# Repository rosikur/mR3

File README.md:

# mR3

## Before we start

I'm so so incredibly Sorry but the firmware was made by an artifical intelligence. This was the result of pixl.hackclub.com shutting down in which I had to finish my Project as soon as possible

## Introduction

Hey Guys! This is my first Music Player Project. The Goal is to learn how to wire
a DAC(Digital Audio Convertor) without Signal Lose. An Amplifier without Noise.
How to power an Stereo Speaker System. How to cnc machine the chassis and how to
fit everything in a compact chassis with a display.

## Components

# ICs:

- TPA6132ARTE
- PAM8403D
- PCM5120A
- ESP32-S3-WROOM-1
- TPS63802DLAR
- BQ25895RTW
- 2.8" Display(See BOM and PINS MAKE SURE YOU BUY one with the same PIN count)

# Periphals

- 3x THT SW Tactile SPST Angeled
- 6x THT SW Push 6mm H5mm
- 1x USB c 2.o Receptaple
- 1x Audio Jack SwitchTR
- 1x 3.7 V Battary Pack (Must be with BMS)
- SD Card Holder (Wuerth)
- 3w Speakers (2)
- Soldering Iron

## How to build it?

# PCB

Firstly take the gerber.zip and upload them to the PCB manufacturer of your choosing, I prefer JLCPCB as i can use the bom in their daughter company lscs to buy the components.
I really recommend to order a stencil with your order because you'll be miserable soldering IC's

Secondly go to LSCS with the bom file and order everything with their MOQ (Minimum Order Quantity) I really recommend to get extra Components 0805s are really common for lots of Projects, if you follow my projects, you can be sure that we'll be using them.

Thirdly, get some solder paste and a Heatplate if you havn't yet else your closest Hackerspace will have some (Props to the C3PB and CCC)

Fourth, open the PCB on your Laptop and grab tweezers and the pcb
put the stencil on (smh) and spread the paste with an old Credit Card. Make sure to put every componet correctly ESPECIALLY THE BATTERY and the IC's (ESP32 are hella expensive.)

Fifth, select a side which will be easier to solder (the back in our case) add everything and put them on the Heatplate or a reflow oven

Lastly make sure to put the battery in correctly THIS IS VERY IMPORTANT. Add the speakers correctly so they dont play in reverse. that should be about it for the pcb onto the case!

# PCB images

# Case

3d print it CNC it idc, i will be uploading the STL , the 3mf the STEP and the cnc file.
I recommend Prototyping with 3d Print and CNC as a finished Product. I will be Posting both results soon!

The Case is now almost finished, I only need to add the buttons,
Here is how it turned out:

# Firmware

Install esp tool or plattform IO press the boot button and plug it into your Computer if you are using Plattform IO you'll have to compile it first ,for esp tool use the ready .bin files :D once its sent to the ESP its ready to use have fun
(Obviously assemble it first)

# BOM

The complete bill of materials is also available as [`bom.csv`](bom.csv).

| Component              | Designators                                             | Footprint                                                    | Qty. | Supplier                                                                                                                         |
| ---------------------- | ------------------------------------------------------- | ------------------------------------------------------------ | ---: | -------------------------------------------------------------------------------------------------------------------------------- |
| 0.47uF                 | C1, C2                                                  | `C_0805_2012Metric_Pad1.18x1.45mm_HandSolder`                |    2 | [Buy](https://www.tme.eu/de/details/cl21b474kafnnng/kondensatoren-mlcc-smd/samsung/)                                             |
| 2.2uF                  | C3, C4, C8, C9                                          | `C_0805_2012Metric_Pad1.18x1.45mm_HandSolder`                |    4 | [Buy](https://www.tme.eu/de/details/0805b225k160ct/kondensatoren-mlcc-smd/walsin/)                                               |
| 0.1uF                  | C5, C6, C14, C15, C16, C19                              | `C_0805_2012Metric_Pad1.18x1.45mm_HandSolder`                |    6 | [Buy](https://www.tme.eu/de/details/0805b104k500ct/kondensatoren-mlcc-smd/walsin/)                                               |
| 1uF                    | C7, C10, C11, C12, C13, C21, C22, C23, C24, C31         | `C_0805_2012Metric_Pad1.18x1.45mm_HandSolder`                |   10 | [Buy](https://www.tme.eu/de/details/0805b105k250ct/kondensatoren-mlcc-smd/walsin/)                                               |
| 10uF                   | C17, C18, C26                                           | `C_0805_2012Metric_Pad1.18x1.45mm_HandSolder`                |    3 | [Buy](https://www.tme.eu/de/details/c0805c106k9pac/kondensatoren-mlcc-smd/kemet/c0805c106k9pactu/)                               |
| 22uF                   | C20, C28, C29, C32, C33, C34                            | `C_0805_2012Metric_Pad1.18x1.45mm_HandSolder`                |    6 | [Buy](https://www.tme.eu/de/details/jmk212abj226mg-t/kondensatoren-mlcc-smd/taiyo-yuden/)                                        |
| 47nF                   | C27                                                     | `C_0805_2012Metric_Pad1.18x1.45mm_HandSolder`                |    1 | [Buy](https://www.tme.eu/de/details/0805b473k500cg/kondensatoren-mlcc-smd/walsin/)                                               |
| 4.7uF                  | C30                                                     | `C_0805_2012Metric_Pad1.18x1.45mm_HandSolder`                |    1 | [Buy](https://www.tme.eu/de/details/0805x475k6r3ct/kondensatoren-mlcc-smd/walsin/)                                               |
| LED                    | D1                                                      | `LED_0805_2012Metric_Pad1.15x1.40mm_HandSolder`              |    1 | [Buy](https://www.tme.eu/de/details/of-smd2012r/led-dioden-smd-bunt/optoflash/)                                                  |
| Micro SD card          | J1                                                      | `microSD_HC_Wuerth_693072010801`                             |    1 | [Buy](https://www.mouser.de/en/ProductDetail/Wurth-Elektronik/693072010801?qs=7gQLVZk5cPmw4uU1mAcUFg%3D%3D)                      |
| Audio jack             | J2                                                      | `Jack_3.5mm_CUI_SJ1-3515N_Horizontal`                        |    1 | [Buy](https://www.tme.eu/de/details/sj13513/klinken-steckverbinder/same-sky-r/sj1-3513/)                                         |
| 9-pin socket _(DNP)_   | J3                                                      | `PinHeader_1x09_P2.54mm_Vertical`                            |    1 | DNP                                                                                                                              |
| USB-C receptacle       | J4                                                      | `USB_C_Receptacle_Amphenol_12401548E4-2A`                    |    1 | [Buy](https://www.mouser.de/en/ProductDetail/Amphenol-Commercial-Products/12401598E42A?qs=367PjNmvCmllVMBVyIyS3w%3D%3D)          |
| 2-pin connector        | J5                                                      | `JST_PH_S2B-PH-K_1x02_P2.00mm_Horizontal`                    |    1 | [Buy](https://www.tme.eu/de/details/s2b-xh-a-1/signalsteckverbinder-raster-2-50mm/jst/s2b-xh-a-1-lf-sn/)                         |
| 2.2uH inductor         | L1                                                      | `L_2512_6332Metric_Pad1.52x3.35mm_HandSolder`                |    1 | [Buy](https://www.mouser.de/en/ProductDetail/Bourns/SRP2512-2R2M?qs=sGAEpiMZZMukHu%252BjC5l7YdTJBteetShHxC51KzP5FBA%3D)          |
| 0.47uH inductor        | L2                                                      | `L_2512_6332Metric_Pad1.52x3.35mm_HandSolder`                |    1 | [Buy](https://www.mouser.de/en/ProductDetail/652-SRP2512-R47M)                                                                   |
| Speaker                | LS1, LS2                                                | `JST_PH_S2B-PH-K_1x02_P2.00mm_Horizontal`                    |    2 | [Buy](https://a.aliexpress.com/_EJix1bo)                                                                                         |
| 10k resistor           | R1, R2, R4, R5, R6, R7, R9, R10, R13, R14, R16, R22–R33 | `R_0805_2012Metric_Pad1.20x1.40mm_HandSolder`                |   23 | [Buy](https://www.tme.eu/de/details/wr08x1002ftl/smd-widerstaende/walsin/)                                                       |
| 5.1k resistor          | R3, R12                                                 | `R_0805_2012Metric_Pad1.20x1.40mm_HandSolder`                |    2 | [Buy](https://www.tme.eu/de/details/wr08x5101ftl/smd-widerstaende/walsin/)                                                       |
| 1k resistor            | R8, R11                                                 | `R_0805_2012Metric_Pad1.20x1.40mm_HandSolder`                |    2 | [Buy](https://www.tme.eu/de/details/wr08x102jtl/smd-widerstaende/walsin/wr08x102-jtl/)                                           |
| 6.8k resistor          | R15                                                     | `R_0805_2012Metric_Pad1.20x1.40mm_HandSolder`                |    1 | [Buy](https://www.tme.eu/de/details/wr08x6801ftl/smd-widerstaende/walsin/)                                                       |
| 2.2k resistor          | R17                                                     | `R_0805_2012Metric_Pad1.20x1.40mm_HandSolder`                |    1 | [Buy](https://www.tme.eu/de/details/wr08x222jtl/smd-widerstaende/walsin/wr08x222-jtl/)                                           |
| 260 ohm resistor       | R18                                                     | `R_0805_2012Metric_Pad1.20x1.40mm_HandSolder`                |    1 | [Buy](https://www.tme.eu/de/details/rc0805fr-07261rl/smd-widerstaende/yageo/)                                                    |
| 100k resistor          | R19                                                     | `R_0805_2012Metric_Pad1.20x1.40mm_HandSolder`                |    1 | [Buy](https://www.tme.eu/de/details/wr08x1003ftl/smd-widerstaende/walsin/)                                                       |
| 91k resistor           | R20                                                     | `R_0805_2012Metric_Pad1.20x1.40mm_HandSolder`                |    1 | [Buy](https://www.mouser.de/en/ProductDetail/Panasonic-Industry/ERJ-6ENF9102V?qs=sGAEpiMZZMtlubZbdhIBIOIpaOjkYUZGTcw3DF91WWo%3D) |
| 511k resistor          | R21                                                     | `R_0805_2012Metric_Pad1.20x1.40mm_HandSolder`                |    1 | [Buy](https://www.tme.eu/de/details/smd0805-511k-1%25/smd-widerstaende/royalohm/0805s8f5113t5e/)                                 |
| Push button            | SW1–SW5, SW9                                            | `SW_PUSH_6mm_H5mm`                                           |    6 | [Buy](https://www.tme.eu/de/details/b3f-1000/mikroschalter-tact/aratas-formerly-omron-components/)                               |
| Angled tactile button  | SW6–SW8                                                 | `SW_Tactile_SPST_Angled_PTS645Vx31-2LFS`                     |    3 | [Buy](https://www.tme.eu/de/details/tacta-64n-f/mikroschalter-tact/ninigi/)                                                      |
| TPA6132A2RTE           | U1                                                      | `WQFN-16-1EP_3x3mm_P0.5mm_EP1.6x1.6mm_ThermalVias`           |    1 | [Buy](https://www.mouser.de/en/ProductDetail/595-TPA6132A2RTET)                                                                  |
| PAM8403D               | U2                                                      | `SOIC-16_3.9x9.9mm_P1.27mm`                                  |    1 | [Buy](https://www.mouser.de/en/ProductDetail/621-PAM8403DR-H)                                                                    |
| PCM5102A               | U3                                                      | `TSSOP-20_4.4x6.5mm_P0.65mm`                                 |    1 | [Buy](https://www.mouser.de/en/ProductDetail/595-PCM5102APWR)                                                                    |
| BQ25895RTW             | U5                                                      | `Texas_RTW_WQFN-24-1EP_4x4mm_P0.5mm_EP2.7x2.7mm_ThermalVias` |    1 | [Buy](https://www.mouser.de/en/ProductDetail/595-BQ25895RTWR)                                                                    |
| TPS63802DLAR           | U6                                                      | `DLA0010A`                                                   |    1 | [Buy](https://www.mouser.de/en/ProductDetail/595-TPS63802DLAR)                                                                   |
| ESP32-S3-WROOM-1       | U7                                                      | `ESP32-S3-WROOM-1`                                           |    1 | [Buy](https://www.mouser.de/en/ProductDetail/356-ESP32S3WROM1N4R8)                                                               |
| Battery                | x                                                       | `LIPo Battary`                                               |    1 | [Buy](https://a.aliexpress.com/_ExininM)                                                                                         |
| Display _(check pins)_ | x                                                       | `TFT Disp`                                                   |    1 | [Buy](https://a.aliexpress.com/_EHwSQO6)                                                                                         |

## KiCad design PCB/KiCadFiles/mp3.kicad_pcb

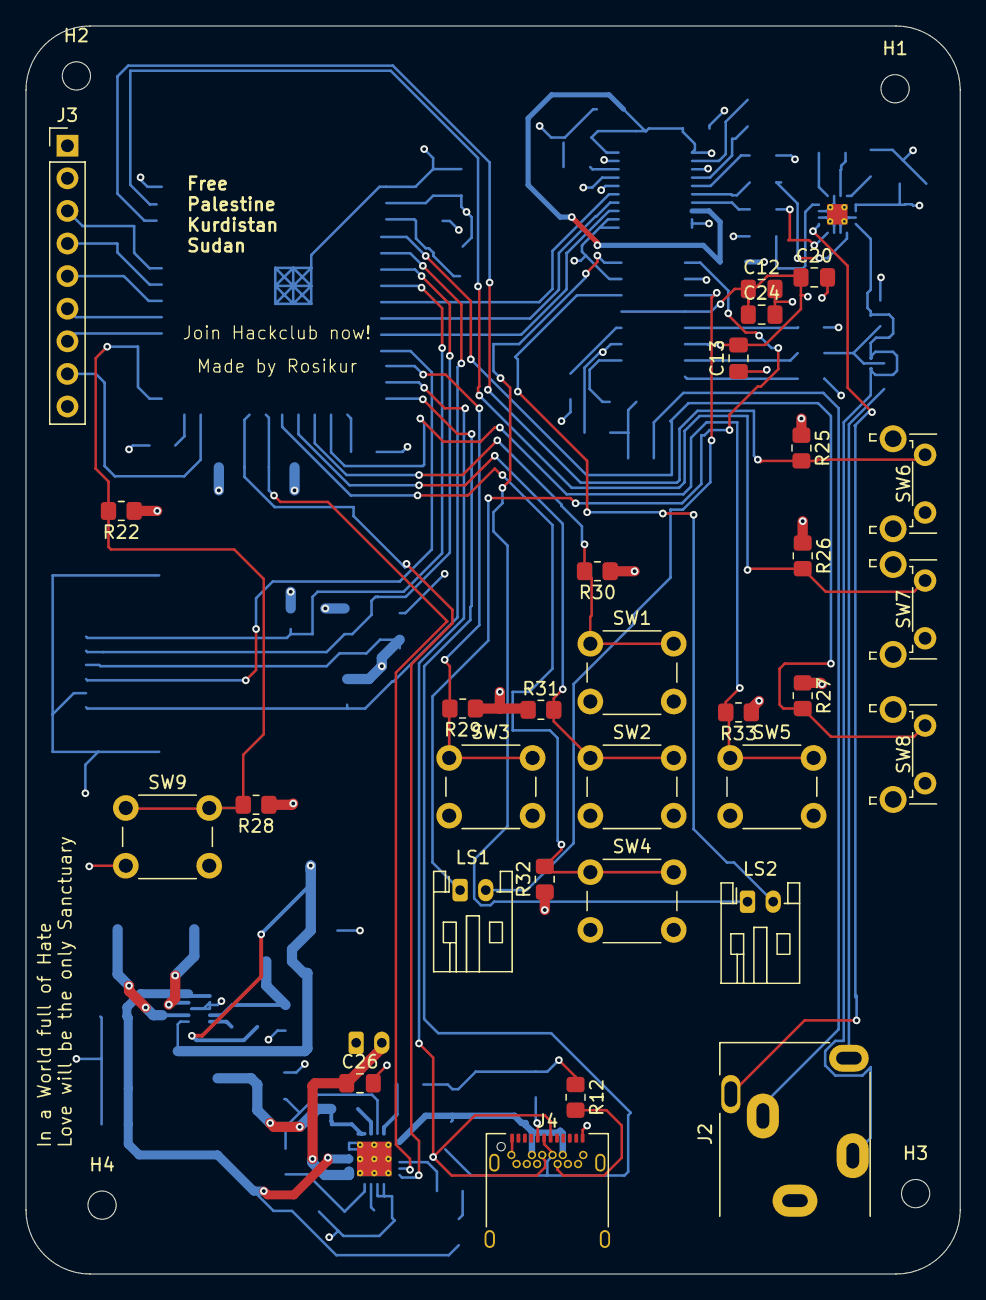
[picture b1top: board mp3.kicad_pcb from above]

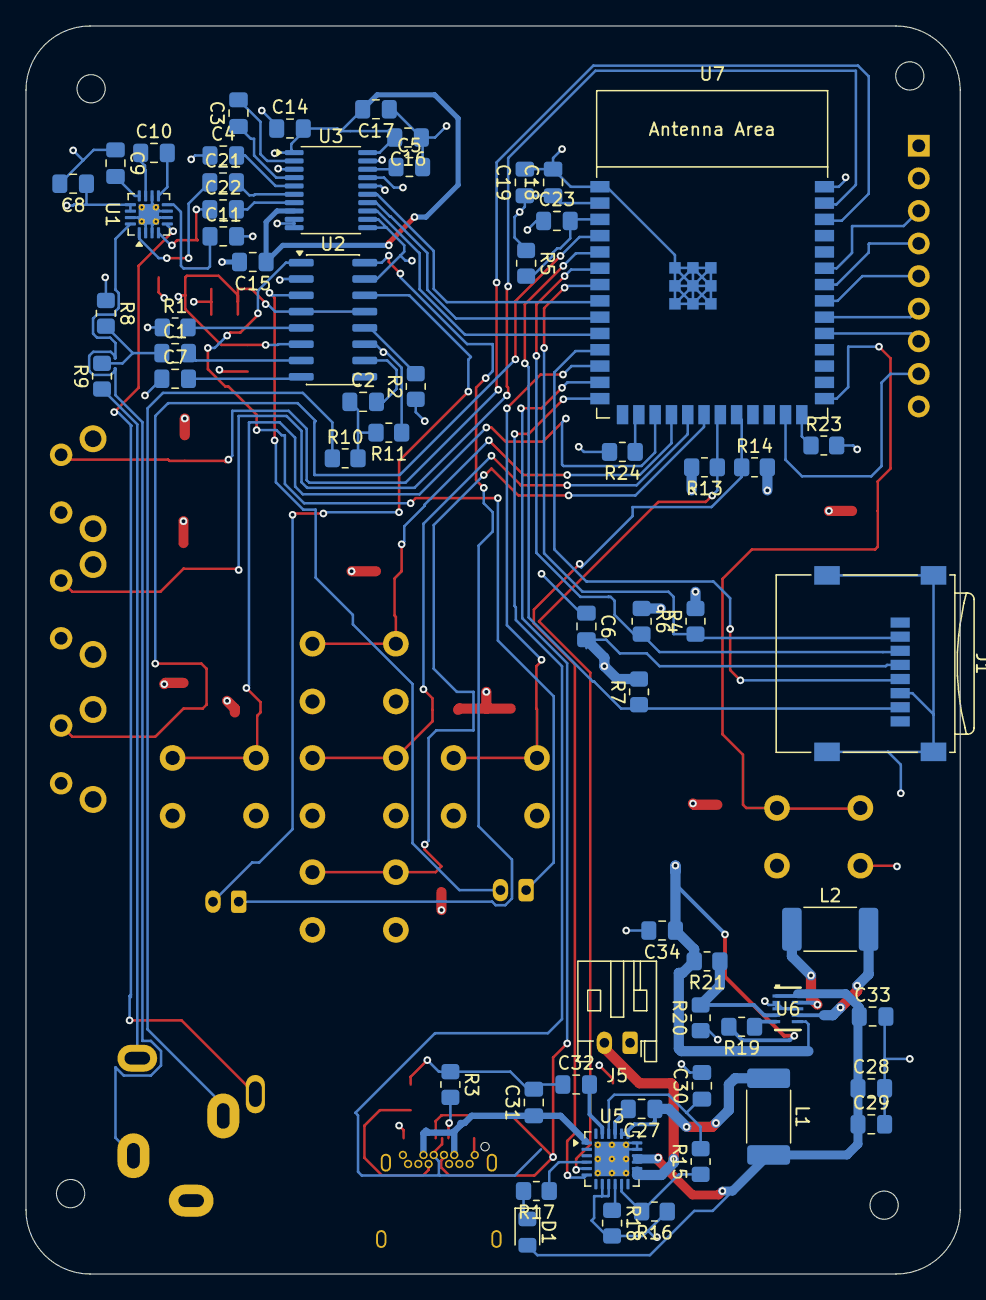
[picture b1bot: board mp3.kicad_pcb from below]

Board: 4 copper layers, 72.8 x 97.3 mm, 95 parts (61 on the bottom side), 75 nets.

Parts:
C1, C2: 0.47uF; C_0805_2012Metric_Pad1.18x1.45mm_HandSolder
C3, C4, C8, C9: 2.2uF; C_0805_2012Metric_Pad1.18x1.45mm_HandSolder
C5, C6, C14, C15, C16, C19: 0.1uF; C_0805_2012Metric_Pad1.18x1.45mm_HandSolder
C7, C10, C11, C12, C13, C21, C22, C23, C24, C31: 1uF; C_0805_2012Metric_Pad1.18x1.45mm_HandSolder
C17, C18, C26: 10uF; C_0805_2012Metric_Pad1.18x1.45mm_HandSolder
C20, C28, C29, C32, C33, C34: 22uF; C_0805_2012Metric_Pad1.18x1.45mm_HandSolder
C27: 47nF; C_0805_2012Metric_Pad1.18x1.45mm_HandSolder
C30: 4.7uF; C_0805_2012Metric_Pad1.18x1.45mm_HandSolder
D1: LED; LED_0805_2012Metric_Pad1.15x1.40mm_HandSolder
H1, H2, H3, H4: MountingHole; MountingHole_2.2mm_M2
J1: Micro_SD_Card; microSD_HC_Wuerth_693072010801
J2: AudioJack3_SwitchTR; Jack_3.5mm_CUI_SJ1-3515N_Horizontal
J3: Conn_01x09_Socket; PinHeader_1x09_P2.54mm_Vertical
J4: USB_C_Receptacle_USB2.0_14P; USB_C_Receptacle_Amphenol_12401548E4-2A
J5: Conn_01x02_Pin; JST_PH_S2B-PH-K_1x02_P2.00mm_Horizontal
L1: 2.2uH; L_2512_6332Metric_Pad1.52x3.35mm_HandSolder
L2: 0.47uH; L_2512_6332Metric_Pad1.52x3.35mm_HandSolder
LS1, LS2: Speaker; JST_PH_S2B-PH-K_1x02_P2.00mm_Horizontal
R1, R2, R9, R10: 10K; R_0805_2012Metric_Pad1.20x1.40mm_HandSolder
R3, R12: 5.1kR; R_0805_2012Metric_Pad1.20x1.40mm_HandSolder
R4, R6, R7: 10kR; R_0805_2012Metric_Pad1.20x1.40mm_HandSolder
R5, R13, R14, R16, R22, R23, R24, R25, R26, R27, R28, R29, R30, R31, R32, R33: 10k; R_0805_2012Metric_Pad1.20x1.40mm_HandSolder
R8, R11: 1k; R_0805_2012Metric_Pad1.20x1.40mm_HandSolder
R15: 6.8k; R_0805_2012Metric_Pad1.20x1.40mm_HandSolder
R17: 2.2k; R_0805_2012Metric_Pad1.20x1.40mm_HandSolder
R18: 260; R_0805_2012Metric_Pad1.20x1.40mm_HandSolder
R19: 100k; R_0805_2012Metric_Pad1.20x1.40mm_HandSolder
R20: 91k; R_0805_2012Metric_Pad1.20x1.40mm_HandSolder
R21: 511k; R_0805_2012Metric_Pad1.20x1.40mm_HandSolder
SW1, SW2, SW3, SW4, SW5, SW9: SW_Push; SW_PUSH_6mm_H5mm
SW6, SW7, SW8: SW_Push; SW_Tactile_SPST_Angled_PTS645Vx31-2LFS
U1: TPA6132A2RTE; WQFN-16-1EP_3x3mm_P0.5mm_EP1.6x1.6mm_ThermalVias
U2: PAM8403D; SOIC-16_3.9x9.9mm_P1.27mm
U3: PCM5102A; TSSOP-20_4.4x6.5mm_P0.65mm
U5: BQ25895RTW; Texas_RTW_WQFN-24-1EP_4x4mm_P0.5mm_EP2.7x2.7mm_ThermalVias
U6: TPS63802DLAR; DLA0010A
U7: ESP32-S3-WROOM-1

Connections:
+3V3: C6.2, C8.1, C12.1, C13.2, C14.2, C15.1, C16.2, C17.2, C18.1, C19.1, C20.1, C24.1, C34.1, J1.4 (VDD), J3.2, R1.1, R2.1, R4.2, R5.1, R6.1, R7.2, R13.2, R14.2, R19.2, R21.2, R22.1, R25.1, R26.1, R27.1, R28.1, R29.1, R30.1, R31.1, R32.1, R33.1, U1.13 (EN), U1.14 (VDD), U2.4 (PVDD), U2.6 (VDD), U2.13 (PVDD), U3.1 (CPVDD), U3.8 (AVDD), U3.17 (XSMT), U3.20 (DVDD), U6.6 (VOUT), U7.2 (3V3)
/BOOT: R22.2, R28.2, SW9.1, U7.27 (IO0)
/BQSCL: R13.1, U5.5 (SCL), U7.21 (IO13)
/BQSDA: R14.1, U5.6 (SDA), U7.22 (IO14)
/CLK: J1.5 (CLK), U7.11 (IO18)
/CMD: J1.3 (CMD), R6.2, U7.6 (IO6)
/D+: J4.A6 (D+), J4.B6 (D+), U5.2 (D+), U7.14 (USB_D+)
/D-: J4.A7 (D-), J4.B7 (D-), U5.3 (D-), U7.13 (USB_D-)
/DACOUTL: C21.1, U1.1 (INL-)
/DACOUTR: C22.1, U1.4 (INR-)
/DAT0: J1.7 (DAT0), R7.1, U7.5 (IO5)
/DAT3: J1.2 (DAT3/CD), R4.1, U7.7 (IO7)
/DISP_BL: J3.8, U7.25 (IO48)
/DISP_CS: J3.7, U7.31 (IO38)
/DISP_DC: J3.6, U7.32 (IO39)
/DISP_RST: J3.5, U7.33 (IO40)
/DISP_SCL: J3.3, U7.35 (IO42)
/DISP_SDA: J3.4, U7.34 (IO41)
/GPIO 14: U3.13 (BCK), U7.10 (IO17)
/GPIO 15: U3.15 (LRCK), U7.8 (IO15)
/GPIO 16: U3.14 (DIN), U7.9 (IO16)
/LOUDER: R25.2, SW6.1, U7.38 (IO2)
/MENU: R30.2, SW1.1, U7.18 (IO10)
/ONOFF: R27.2, SW8.1, U7.4 (IO4)
/OUTL: J2.T, U1.16 (OUTL)
/OUTR: J2.R, U1.5 (OUTR)
/PLAY: R32.2, SW4.1, U7.20 (IO12)
/QUIETER: R26.2, SW7.1, U7.39 (IO1)
/SEL: R31.2, SW2.1, U7.19 (IO11)
/SKIP: R33.2, SW5.1, U7.17 (IO9)
/SYS: C28.1, C29.1, C33.1, D1.2 (A), L1.2, U5.15 (SYS), U5.16 (SYS), U6.1 (EN), U6.10 (VIN)
/UNSKIP: R29.2, SW3.1, U7.12 (IO8)
/VBUS: C31.1, J4.A4 (VBUS), J4.A9 (VBUS), J4.B4 (VBUS), J4.B9 (VBUS), U5.1 (VBUS)
GND: C4.1, C5.2, C6.1, C7.1, C8.2, C9.1, C11.2, C12.2, C13.1, C14.1, C15.2, C16.1, C17.1, C18.2, C19.2, C20.2, C23.1, C24.2, C26.2, C28.2, C29.2, C30.2, C31.2, C32.1, C33.2, C34.2, J1.6 (VSS), J1.SH (SHIELD), J2.S, J3.1, J4.A1 (GND), J4.A12 (GND), J4.B1 (GND), J4.B12 (GND), J4.SH (SHIELD), J5.1, R3.1, R8.1, R11.1, R12.1, R16.1, R18.2, R20.1, R23.2, R24.2, SW1.2, SW2.2, SW3.2, SW4.2, SW5.2, SW6.2, SW7.2, SW8.2, SW9.2, U1.2 (INL+), U1.3 (INR+), U1.6 (G0), U1.7 (G1), U1.10 (PGND), U1.15 (SGND), U1.17 (EP), U2.2 (PGND), U2.11 (GND), U2.15 (PGND), U3.3 (CPGND), U3.9 (AGND), U3.10 (DEMP), U3.11 (FLT), U3.12 (SCK), U3.16 (FMT), U3.19 (DGND), U5.8 (OTG), U5.9 (~CE), U5.17 (PGND), U5.18 (PGND), U5.25 (PGND), U6.2 (MODE), U6.3 (AGND), U6.8 (GND), U7.1 (GND), U7.40 (GND), U7.41 (GND)
unnamed: C1.1, R8.2, R9.2
unnamed: C2.1, R10.2, R11.2
unnamed: C27.1, L1.1, U5.19 (SW), U5.20 (SW)
unnamed: D1.1 (K), R17.2
unnamed: J2.RN, R10.1
unnamed: J2.TN, R9.1
unnamed: J4.A5 (CC1), R3.2
unnamed: J4.B5 (CC2), R12.2
unnamed: C26.1, J5.2, U5.13 (BAT), U5.14 (BAT)
unnamed: C10.2, U1.9 (CPN)
unnamed: C10.1, U1.11 (CPP)
unnamed: C9.2, U1.12 (HPVDD)
unnamed: C11.1, U1.8 (HPVSS)
unnamed: C1.2, U2.7 (INL)
unnamed: C2.2, U2.10 (INR)
unnamed: LS1.1, U2.1 (LOUT+)
unnamed: LS1.2, U2.3 (LOUT-)
unnamed: LS2.1, U2.16 (ROUT+)
unnamed: LS2.2, U2.14 (ROUT-)
unnamed: C7.2, U2.8 (VREF)
unnamed: R1.2, U2.5 (~MUTE)
unnamed: R2.2, U2.12 (~SHDN)
unnamed: C3.1, U3.4 (CAPM)
unnamed: C3.2, U3.2 (CAPP)
unnamed: C5.1, U3.18 (LDOO)
unnamed: C21.2, U3.6 (OUTL)
unnamed: C22.2, U3.7 (OUTR)
unnamed: C4.2, U3.5 (VNEG)
unnamed: C27.2, U5.21 (BTST)
unnamed: R18.1, U5.10 (ILIM)
unnamed: C32.2, U5.23 (PMID)
unnamed: C30.1, R15.2, U5.22 (REGN)
unnamed: R17.1, U5.4 (STAT)
unnamed: R15.1, R16.2, U5.11 (TS)
unnamed: R20.2, R21.1, U6.4 (FB)
unnamed: L2.1, U6.9 (L1)
unnamed: L2.2, U6.7 (L2)
unnamed: R19.1, U6.5 (PG)
unnamed: C23.2, R5.2, U7.3 (EN)
unnamed: R23.1, U7.26 (IO45)
unnamed: R24.1, U7.16 (IO46)

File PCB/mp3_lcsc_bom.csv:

Comment,Designator,Footprint,Quantity,LINK
0.47uF,"C1, C2",C_0805_2012Metric_Pad1.18x1.45mm_HandSolder,2,https://www.tme.eu/de/details/cl21b474kafnnng/kondensatoren-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
2.2uF,"C3, C4, C8, C9",C_0805_2012Metric_Pad1.18x1.45mm_HandSolder,4,https://www.tme.eu/de/details/0805b225k160ct/kondensatoren-m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
0.1uF,"C5, C6, C14, C15, C16, C19",C_0805_2012Metric_Pad1.18x1.45mm_HandSolder,6,https://www.tme.eu/de/details/0805b104k500ct/kondensatoren-m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
1uF,"C7, C10, C11, C12, C13, C21, C22, C23, C24, C31",C_0805_2012Metric_Pad1.18x1.45mm_HandSolder,10,https://www.tme.eu/de/details/0805b105k250ct/kondensatoren-m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
10uF,"C17, C18, C26",C_0805_2012Metric_Pad1.18x1.45mm_HandSolder,3,https://www.tme.eu/de/details/c0805c106k9pac/kondensatoren-m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
22uF,"C20, C28, C29, C32, C33, C34",C_0805_2012Metric_Pad1.18x1.45mm_HandSolder,6,https://www.tme.eu/de/details/jmk212abj226mg-t/kondensatoren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
47nF,C27,C_0805_2012Metric_Pad1.18x1.45mm_HandSolder,1,https://www.tme.eu/de/details/0805b473k500cg/kondensatoren-m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
4.7uF,C30,C_0805_2012Metric_Pad1.18x1.45mm_HandSolder,1,https://www.tme.eu/de/details/0805x475k6r3ct/kondensatoren-m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
LED,D1,LED_0805_2012Metric_Pad1.15x1.40mm_HandSolder,1,https://www.tme.eu/de/details/of-smd2012r/led-dioden-smd-bun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
Micro_SD_Card,J1,microSD_HC_Wuerth_693072010801,1,https://www.mouser.de/en/ProductDetail/Wurth-Elektronik/6930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
AudioJack3_SwitchTR,J2,Jack_3.5mm_CUI_SJ1-3515N_Horizontal,1,https://www.tme.eu/de/details/sj13513/klinken-steckverbinder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
Conn_01x09_Socket DNP,J3,PinHeader_1x09_P2.54mm_Vertical,1,DNP
USB_C_Receptacle_USB2.0_14P,J4,USB_C_Receptacle_Amphenol_12401548E4-2A,1,https://www.mouser.de/en/ProductDetail/Amphenol-Commercial-P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
Conn_01x02_Pin,J5,JST_PH_S2B-PH-K_1x02_P2.00mm_Horizontal,1,https://www.tme.eu/de/details/s2b-xh-a-1/signalsteckverbinde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
2.2uH,L1,L_2512_6332Metric_Pad1.52x3.35mm_HandSolder,1,https://www.mouser.de/en/ProductDetail/Bourns/SRP2512-2R2M?q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
0.47uH,L2,L_2512_6332Metric_Pad1.52x3.35mm_HandSolder,1,https://www.mouser.de/en/ProductDetail/652-SRP2512-R47M
Speaker,"LS1, LS2",JST_PH_S2B-PH-K_1x02_P2.00mm_Horizontal,2,https://a.aliexpress.com/_EJix1bo
10k,"R1, R2, R4, R5, R6, R7, R9, R10, R13, R14, R16, R22, R23, R24, R25, R26, R27, R28, R29, R30, R31, R32, R33",R_0805_2012Metric_Pad1.20x1.40mm_HandSolder,23,https://www.tme.eu/de/details/wr08x1002ftl/smd-widerstaende/walsin/
5.1k,"R3, R12",R_0805_2012Metric_Pad1.20x1.40mm_HandSolder,2,https://www.tme.eu/de/details/wr08x5101ftl/smd-widerstaende/walsin/
1k,"R8, R11",R_0805_2012Metric_Pad1.20x1.40mm_HandSolder,2,https://www.tme.eu/de/details/wr08x102jtl/smd-widerstaende/w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
6.8k,R15,R_0805_2012Metric_Pad1.20x1.40mm_HandSolder,1,https://www.tme.eu/de/details/wr08x6801ftl/smd-widerstaende/walsin/
2.2k,R17,R_0805_2012Metric_Pad1.20x1.40mm_HandSolder,1,https://www.tme.eu/de/details/wr08x222jtl/smd-widerstaende/w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
260,R18,R_0805_2012Metric_Pad1.20x1.40mm_HandSolder,1,https://www.tme.eu/de/details/rc0805fr-07261rl/smd-widerstae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
100k,R19,R_0805_2012Metric_Pad1.20x1.40mm_HandSolder,1,https://www.tme.eu/de/details/wr08x1003ftl/smd-widerstaende/walsin/
91k,R20,R_0805_2012Metric_Pad1.20x1.40mm_HandSolder,1,https://www.mouser.de/en/ProductDetail/Panasonic-Industry/ER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
511k,R21,R_0805_2012Metric_Pad1.20x1.40mm_HandSolder,1,https://www.tme.eu/de/details/smd0805-511k-1%25/smd-widersta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
SW_Push,"SW1, SW2, SW3, SW4, SW5, SW9",SW_PUSH_6mm_H5mm,6,https://www.tme.eu/de/details/b3f-1000/mikroschalter-tact/ar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
SW_Push,"SW6, SW7, SW8",SW_Tactile_SPST_Angled_PTS645Vx31-2LFS,3,https://www.tme.eu/de/details/tacta-64n-f/mikroschalter-tact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
TPA6132A2RTE,U1,WQFN-16-1EP_3x3mm_P0.5mm_EP1.6x1.6mm_ThermalVias,1,https://www.mouser.de/en/ProductDetail/595-TPA6132A2RTET
PAM8403D,U2,SOIC-16_3.9x9.9mm_P1.27mm,1,https://www.mouser.de/en/ProductDetail/621-PAM8403DR-H
PCM5102A,U3,TSSOP-20_4.4x6.5mm_P0.65mm,1,https://www.mouser.de/en/ProductDetail/595-PCM5102APWR
BQ25895RTW,U5,Texas_RTW_WQFN-24-1EP_4x4mm_P0.5mm_EP2.7x2.7mm_ThermalVias,1,https://www.mouser.de/en/ProductDetail/595-BQ25895RTWR
TPS63802DLAR,U6,DLA0010A,1,https://www.mouser.de/en/ProductDetail/595-TPS63802DLAR
ESP32-S3-WROOM-1,U7,ESP32-S3-WROOM-1,1,https://www.mouser.de/en/ProductDetail/356-ESP32S3WROM1N4R8
Battery,x,LIPo Battary,1,https://a.aliexpress.com/_ExininM
Display (Check Pins),x,TFT Disp,1,https://a.aliexpress.com/_EHwSQO6

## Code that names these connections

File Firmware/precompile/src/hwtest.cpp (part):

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  int8_t pin;
};
constexpr Btn BTNS[] = {
    {"MENU", pins::BTN_MENU},       {"SEL", pins::BTN_SEL},      {"PLAY", pins::BTN_PLAY},
    {"SKIP", pins::BTN_SKIP},       {"UNSKIP", pins::BTN_UNSKIP}, {"LOUDER", pins::BTN_LOUDER},
    {"QUIETER", pins::BTN_QUIETER}, {"ONOFF", pins::BTN_ONOFF},  {"BOOT", pins::BTN_BOOT},
};
constexpr size_t NBTN = sizeof(BTNS) / sizeof(BTNS[0]);
int8_t lastState[NBTN];
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
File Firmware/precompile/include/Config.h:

#pragma once
#include <stdint.h>

// mR3 hardware configuration. Source: mp3.kicad_sch (ESP32-S3-WROOM-1).
// Change pins here only.

namespace mr3 {

// Firmware identity (used by the About screen)
constexpr const char* FW_NAME     = "mR3 OS";
constexpr const char* FW_VERSION  = "0.2.0";
constexpr const char* FW_CODENAME = "Snickerdoodle";

// Audio volume steps used by ESP32-audioI2S (0..VOLUME_STEPS)
constexpr int VOLUME_STEPS = 21;

// BQ25895 charger I2C address (7-bit)
constexpr uint8_t BQ_ADDR = 0x6A;

namespace pins {

// Display (J3, 4-wire SPI, no MISO, no touch). Controller assumed ILI9341 240x320.
// TFT_eSPI takes its pins from the -DTFT_* build flags in platformio.ini. Those are
// preprocessor macros, so the constants here must NOT be called TFT_SCLK etc. (the macro
// would turn "constexpr int8_t TFT_SCLK = 42;" into "constexpr int8_t 42 = 42;").
// The static_asserts at the end of this file keep both copies in sync.
constexpr int8_t DISP_SCLK = 42;
constexpr int8_t DISP_MOSI = 41;
constexpr int8_t DISP_DC   = 39;
constexpr int8_t DISP_CS   = 38;
constexpr int8_t DISP_RST  = 40;
constexpr int8_t TFT_BL    = 48;  // backlight PWM is driven by the firmware, not by TFT_eSPI

// microSD (J1), SDMMC 1-bit. DAT3 is only pulled up, DAT1/DAT2 unconnected.
constexpr int8_t SD_CLK = 18;
constexpr int8_t SD_CMD = 6;
constexpr int8_t SD_D0  = 5;

// PCM5102A DAC (U3). Note: schematic net labels say "GPIO 14/15/16", real pins below.
constexpr int8_t I2S_BCK  = 17;  // U3.13 BCK
constexpr int8_t I2S_WS   = 15;  // U3.15 LRCK
constexpr int8_t I2S_DOUT = 16;  // U3.14 DIN

// BQ25895 charger (U5), I2C address 0x6A. INT/QON not connected.
constexpr int8_t BQ_SDA = 14;
constexpr int8_t BQ_SCL = 13;

// Buttons: active low, external 10k pull-ups to 3V3.
constexpr int8_t BTN_MENU    = 10;
constexpr int8_t BTN_SEL     = 11;
constexpr int8_t BTN_PLAY    = 12;
constexpr int8_t BTN_SKIP    = 9;   // next
constexpr int8_t BTN_UNSKIP  = 8;   // previous
constexpr int8_t BTN_LOUDER  = 2;
constexpr int8_t BTN_QUIETER = 1;
constexpr int8_t BTN_ONOFF   = 4;
constexpr int8_t BTN_BOOT    = 0;

} // namespace pins
} // namespace mr3

// Fail the build if platformio.ini and this file ever disagree about the display wiring.
#if defined(TFT_SCLK)
static_assert(TFT_SCLK == mr3::pins::DISP_SCLK, "TFT_SCLK in platformio.ini differs from Config.h");
#endif
#if defined(TFT_MOSI)
static_assert(TFT_MOSI == mr3::pins::DISP_MOSI, "TFT_MOSI in platformio.ini differs from Config.h");
#endif
#if defined(TFT_DC)
static_assert(TFT_DC == mr3::pins::DISP_DC, "TFT_DC in platformio.ini differs from Config.h");
#endif
#if defined(TFT_CS)
static_assert(TFT_CS == mr3::pins::DISP_CS, "TFT_CS in platformio.ini differs from Config.h");
#endif
#if defined(TFT_RST)
static_assert(TFT_RST == mr3::pins::DISP_RST, "TFT_RST in platformio.ini differs from Config.h");
#endif
